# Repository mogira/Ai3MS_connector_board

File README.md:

# Anycubic i3 Mega S Connector Board
## Overview
This is the project to create the connector board for ["MONOBLOCK" ANYUCBIC I3 MEGA-S Direct Extruder MOD add BLTouch by Toshi_Yamamoto](https://www.thingiverse.com/thing:4035830).  
The board accepts BLTouch, Extruder Motor and the extension cords to these from motherboard additinally.

### Remarks
**If you need switch, capacitors and resistors of the stock board, you can not use this board because I removed them.**

<br />

## [>> Build Guide](docs/build_guide.md)

<br />

## [>> CADLAB.io](https://cadlab.io/node/23246/)

<br />

## [>> Circuit Board Gallery](docs/circuit_board_gallery.md)

<br />

## Gallery

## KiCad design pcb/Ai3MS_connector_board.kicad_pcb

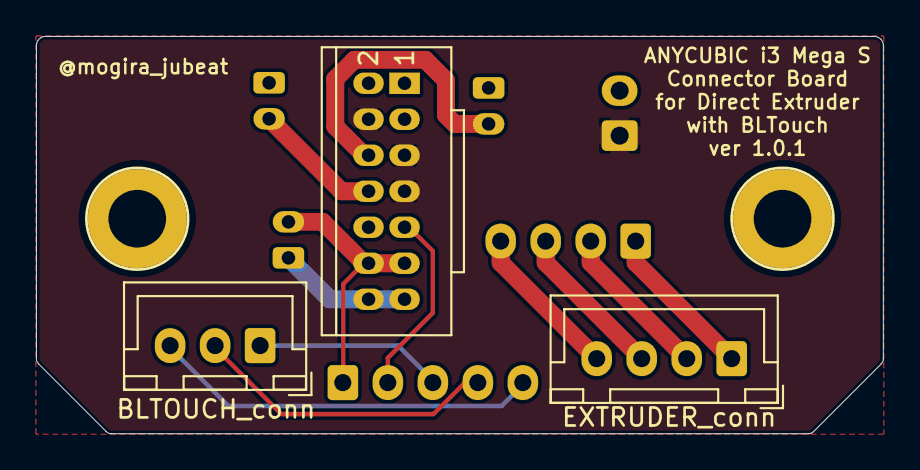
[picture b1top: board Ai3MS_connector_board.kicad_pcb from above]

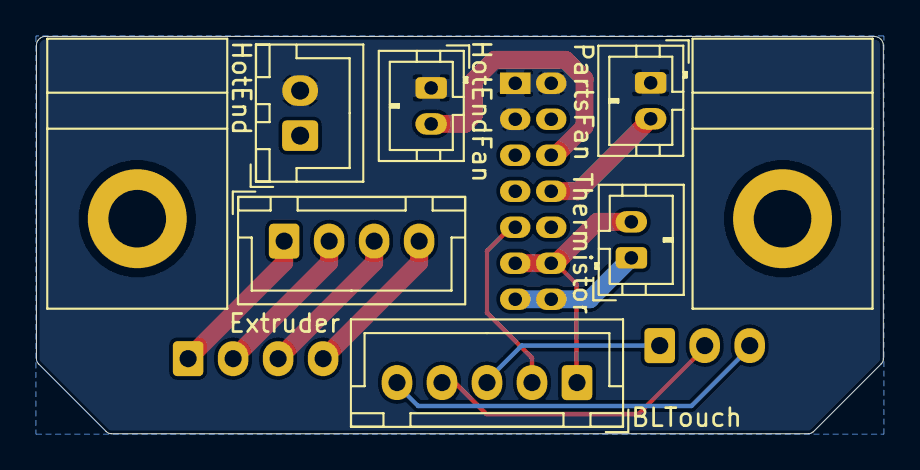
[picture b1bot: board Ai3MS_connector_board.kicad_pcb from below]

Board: 2 copper layers, 47.0 x 22.1 mm, 9 parts (6 on the bottom side), 14 nets.

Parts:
BLTOUCH_conn: 1x3_rev; JST_XH_B3B-XH-A_1x03_P2.50mm_Vertical
BLTouch: 1x5; JST_XH_B5B-XH-A_1x05_P2.50mm_Vertical
EXTRUDER_conn: 1x4_rev; JST_XH_B4B-XH-A_1x04_P2.50mm_Vertical
Extruder: 1x4; JST_XH_B4B-XH-A_1x04_P2.50mm_Vertical
HotEnd: 1x2; JST_XH_B2B-XH-A_1x02_P2.50mm_Vertical
HotEndFan: 1x2; JST_PH_B2B-PH-K_1x02_P2.00mm_Vertical
J1: 2x7; 2x7_2mm-pitch_Lock_GreenConnector
PartsFan: 1x2; JST_PH_B2B-PH-K_1x02_P2.00mm_Vertical
Thermistor: 1x2; JST_PH_B2B-PH-K_1x02_P2.00mm_Vertical

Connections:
/BLTOUCH1_SERVO_5V: BLTOUCH_conn.3, BLTouch.5
/BLTOUCH1_SERVO_CONTROL: BLTOUCH_conn.1, BLTouch.3
/BLTOUCH1_SERVO_GND: BLTOUCH_conn.2, BLTouch.4
/EXTRUDER1_A+: EXTRUDER_conn.1, Extruder.1
/EXTRUDER1_A-: EXTRUDER_conn.2, Extruder.2
/EXTRUDER1_B+: EXTRUDER_conn.3, Extruder.3
/EXTRUDER1_B-: EXTRUDER_conn.4, Extruder.4
BLTOUCH1_GND: BLTouch.1, J1.11, J1.12, Thermistor.2
BLTOUCH1_ZMIN: BLTouch.2, J1.9
HEATER1_12V: HotEnd.2, HotEndFan.1, J1.1, J1.2, J1.3, PartsFan.1
HEATER1_GND: HotEnd.1, J1.4, J1.5, J1.7
HOTENDFAN1_GND: HotEndFan.2, J1.6
PARTFAN1_GND: J1.8, PartsFan.2
THERMISTOR1_DATA: J1.13, J1.14, Thermistor.1

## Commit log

2020-08-11 Reproduce the electrical connection of the stock board
2020-08-11 Add EXTRUDER and BLTOUCH
2020-08-11 Remove SWITCH, Capacitors and Resistors
2020-08-11 Add connection_memo.md
2020-08-22 Move kicad files to "pcb" directory
2020-08-22 v1.0.0
2020-08-25 Add backlink to CADLAB.io
2020-09-01 Export symbols and footprints to libraries
2020-09-08 Improve AXA-15-M3
    * Fix hole size
    * Add backside silk for the screw head
    * Add 0.5mm local clearance for the pad
    * Add 3d model
2020-09-08 Improve links
    * Change link names
    * Change connection paths
    * Retouch PCB due to loading new net file
    * Note: HEATER's 12V/GND is inversed of others. Pin#1 is GND, Pin#2 is 12V.
2020-09-08 Round four corners
2020-09-08 Improve 2x7_2mm-pitch_Lock_GreenConnector
    * Renamed from "PHLike_Green_Connector"
    * Fix pin assign of symbol "2x7"
    * Fix pin assign of footprint "2x7_2mm-pitch_Lock_GreenConnector"
    * Update silk
    * Add 3d model
2020-09-09 Fix upper right silk
    * From "ANYCUBIC i3 Mega" to "ANYCUBIC i3 Mega S"
    * Update version string
2020-09-09 Generate drill and gerber files
2020-10-06 Modify the documents
